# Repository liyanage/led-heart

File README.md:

Arduino LED Heart, see https://hackaday.io/project/8129-led-heart

Some code based on https://github.com/einsteinx2/arduino_heart

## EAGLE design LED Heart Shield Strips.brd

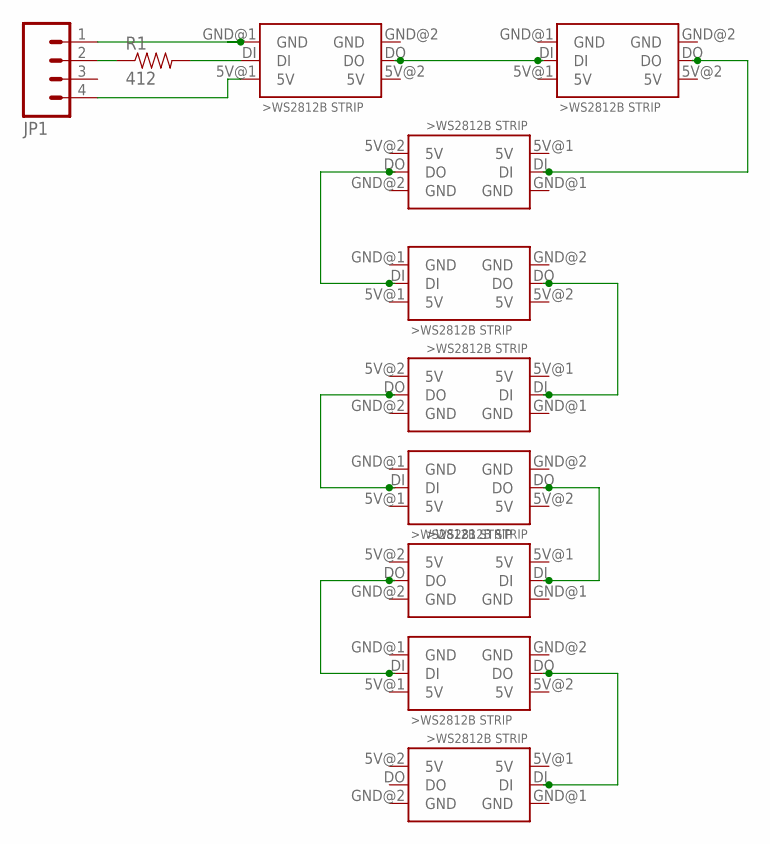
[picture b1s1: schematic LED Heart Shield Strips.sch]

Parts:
IC1, IC2, IC8: WS2812BSTRIP602; WS2812BSTRIP60_2
IC3, IC4: WS2812BSTRIP606; WS2812BSTRIP60_6
IC5: WS2812BSTRIP605; WS2812BSTRIP60_5
IC6: WS2812BSTRIP604; WS2812BSTRIP60_4
IC7: WS2812BSTRIP603; WS2812BSTRIP60_3
IC9: WS2812BSTRIP601; WS2812BSTRIP60_1
JP1: M04NO_SILK_ALL_ROUND; 1X04_NO_SILK_ALL_ROUND
R1: 412; 1206

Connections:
5V: IC1.5V@2 (5V), IC2.5V@1 (5V), IC2.5V@2 (5V), IC3.5V@1 (5V), IC3.5V@2 (5V), IC4.5V@1 (5V), IC4.5V@2 (5V), IC5.5V@1 (5V), IC5.5V@2 (5V), IC6.5V@1 (5V), IC6.5V@2 (5V), IC7.5V@1 (5V), IC7.5V@2 (5V), IC8.5V@1 (5V), IC8.5V@2 (5V), IC9.5V@1 (5V), IC9.5V@2 (5V)
GND: IC1.GND@2 (GND), IC2.GND@1 (GND), IC2.GND@2 (GND), IC3.GND@1 (GND), IC3.GND@2 (GND), IC4.GND@1 (GND), IC4.GND@2 (GND), IC5.GND@1 (GND), IC5.GND@2 (GND), IC6.GND@1 (GND), IC6.GND@2 (GND), IC7.GND@1 (GND), IC7.GND@2 (GND), IC8.GND@1 (GND), IC8.GND@2 (GND), IC9.GND@1 (GND), IC9.GND@2 (GND)
unnamed: IC1.GND@1 (GND), JP1.1
unnamed: IC1.DO, IC2.DI
unnamed: IC2.DO, IC3.DI
unnamed: IC1.5V@1 (5V), JP1.4
unnamed: IC1.DI, R1.2
unnamed: IC3.DO, IC4.DI
unnamed: IC4.DO, IC5.DI
unnamed: IC5.DO, IC6.DI
unnamed: IC6.DO, IC7.DI
unnamed: IC7.DO, IC8.DI
unnamed: IC8.DO, IC9.DI
unnamed: JP1.2, R1.1

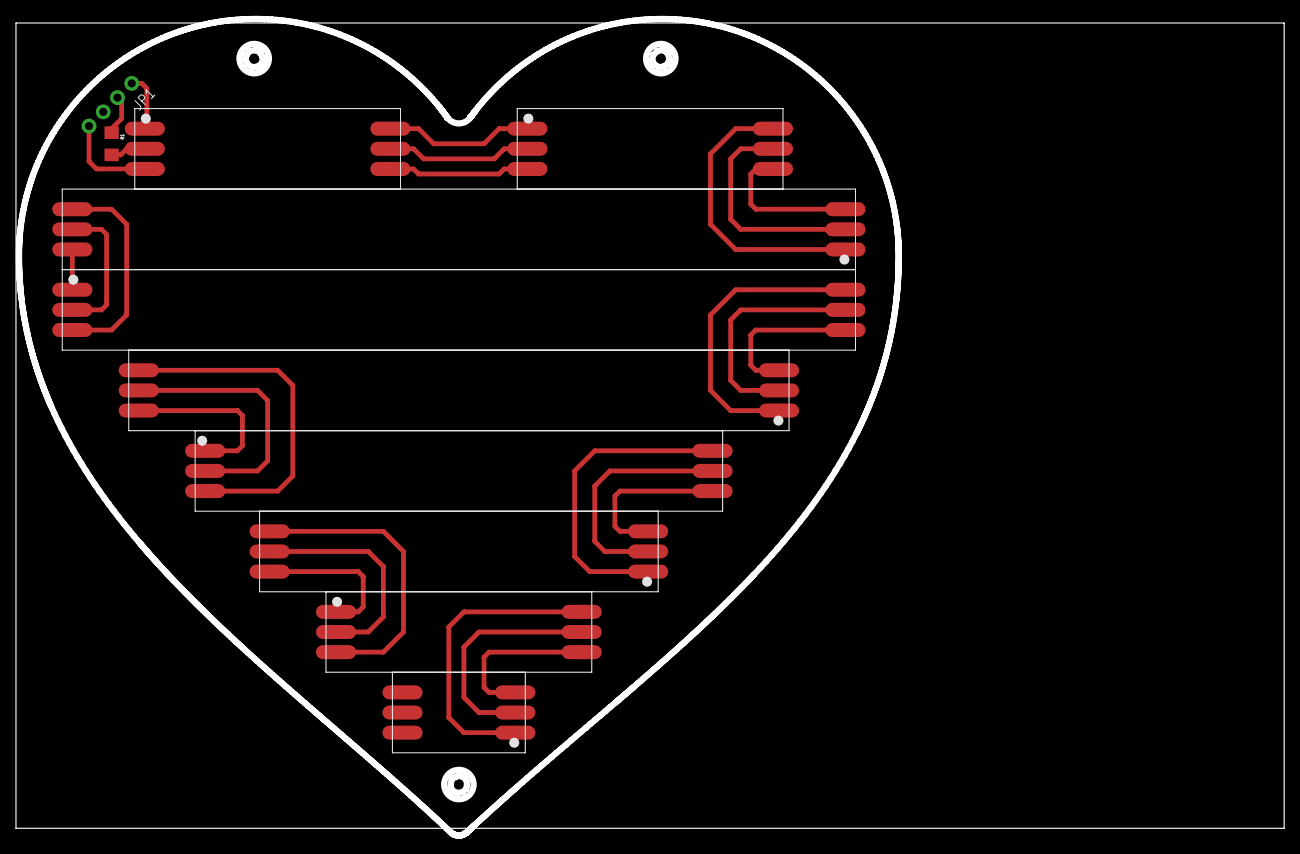
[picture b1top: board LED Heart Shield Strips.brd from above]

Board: 2 copper layers, 160.0 x 103.0 mm, 11 parts (0 on the bottom side), 14 nets.

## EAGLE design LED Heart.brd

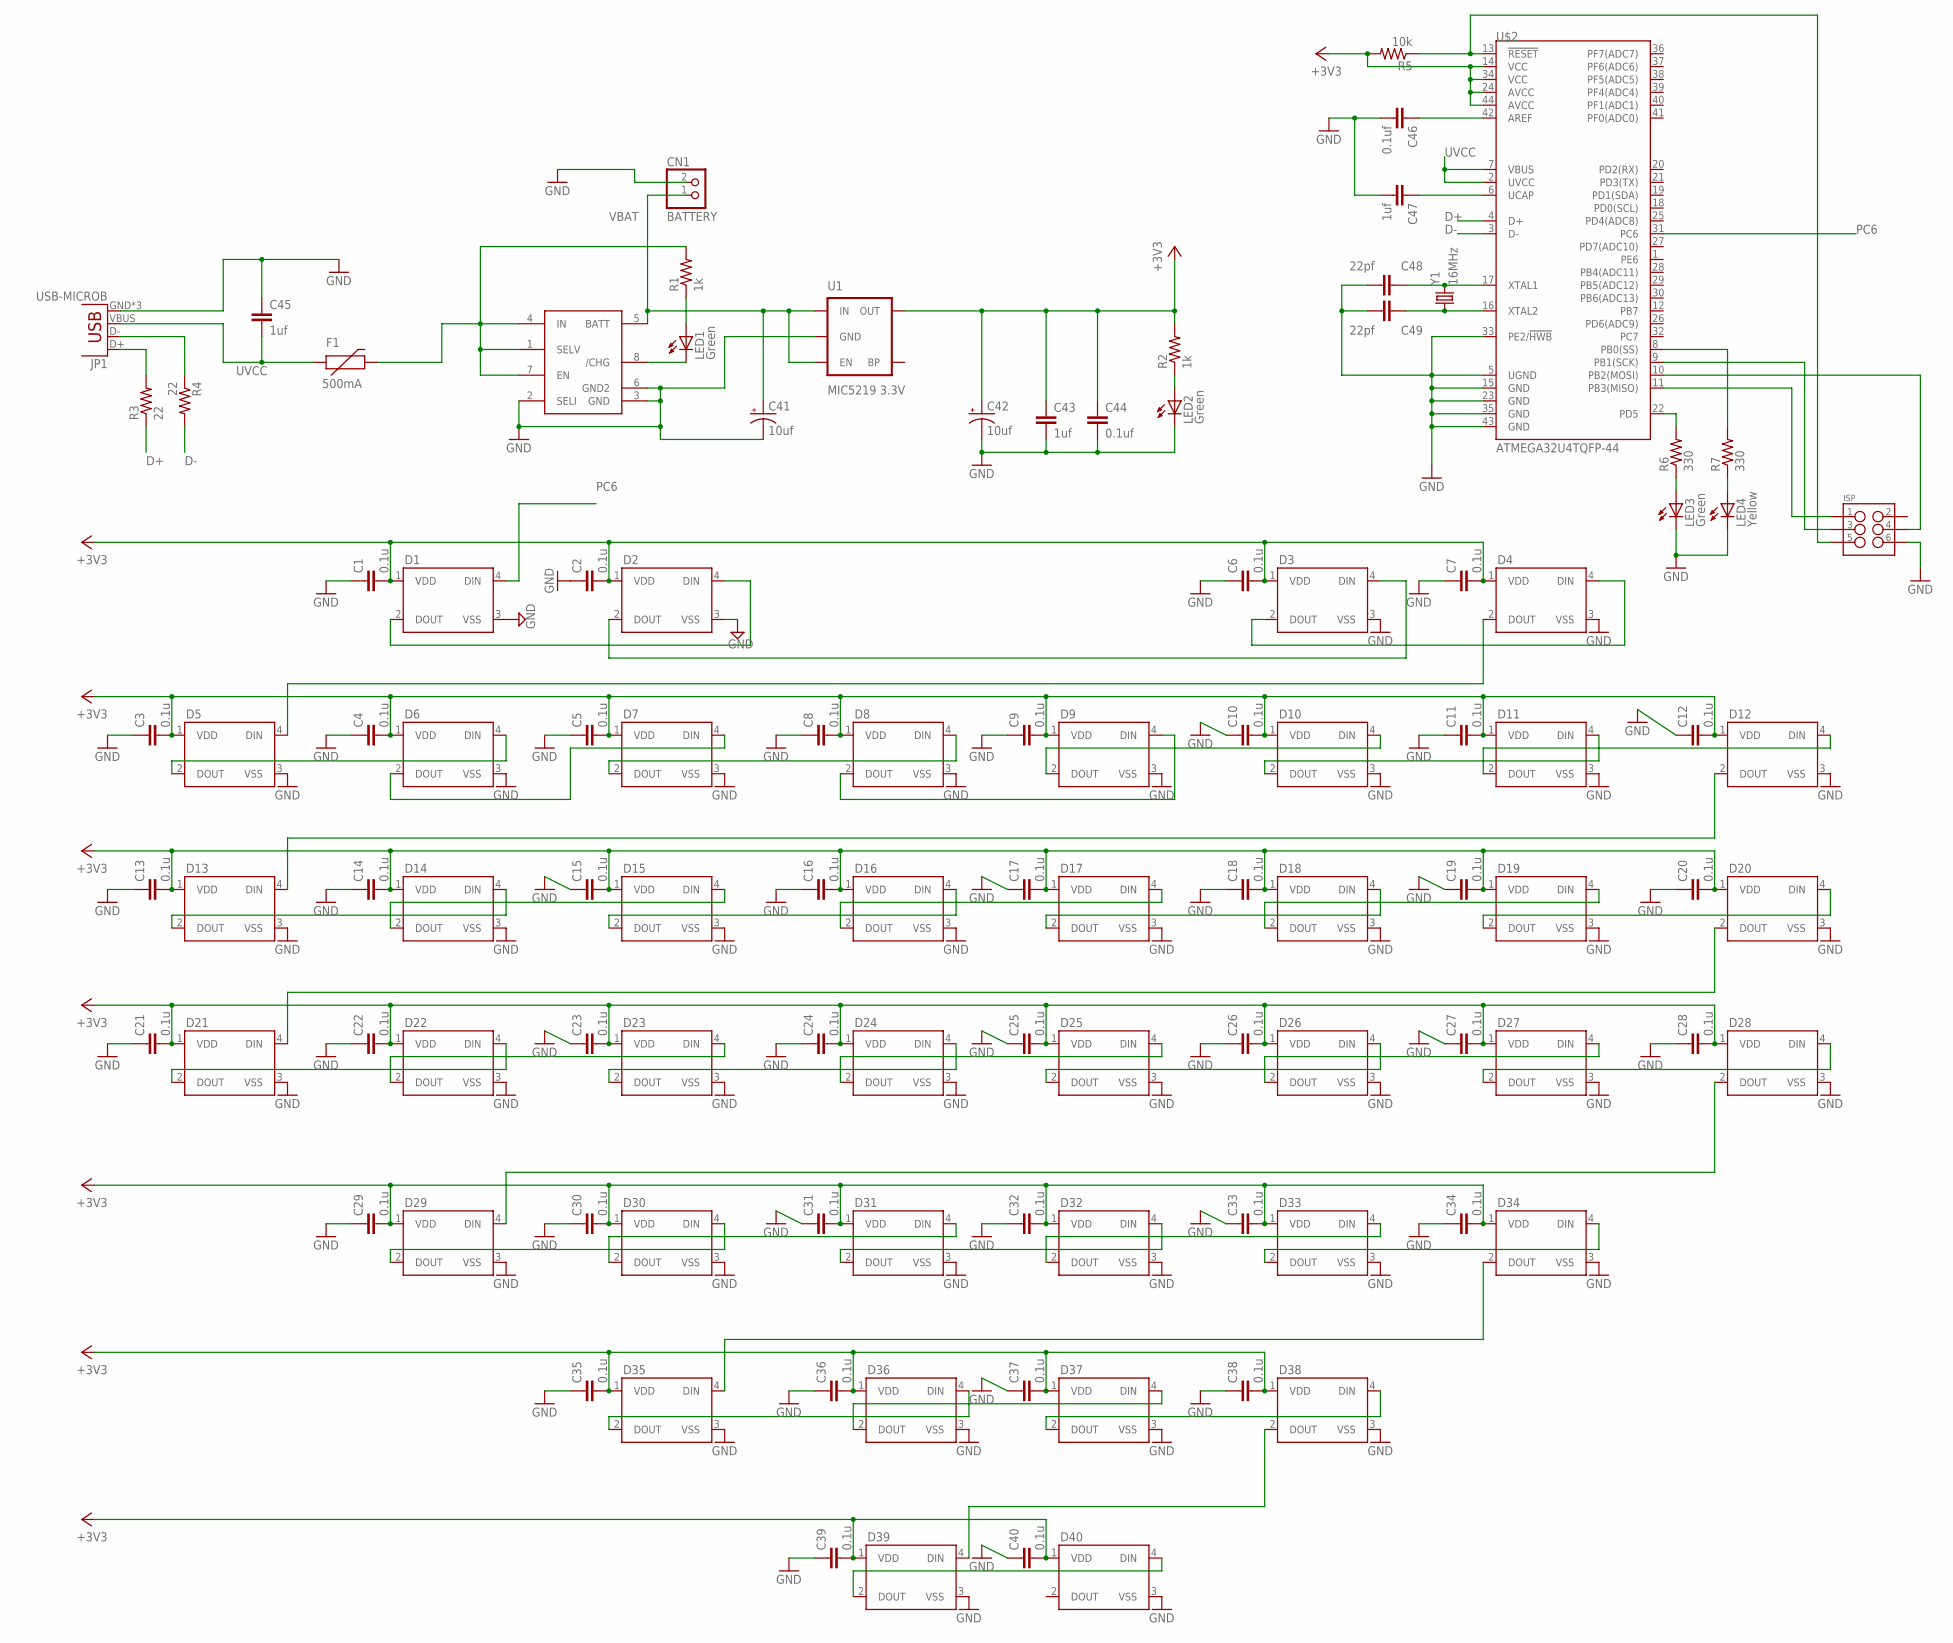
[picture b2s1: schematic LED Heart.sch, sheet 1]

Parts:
C1, C2, C3, C4, C5, C6, C7, C8, C9, C10, C11, C12, C13, C14, C15, C16, C17, C18, C19, C20, C21, C22, C23, C24, C25, C26, C27, C28, C29, C30, C31, C32, C33, C34, C35, C36, C37, C38, C39, C40: 0.1u; 0805
C41, C42: 10uf; EIA3216
C43, C45, C47: 1uf; 0805
C44, C46: 0.1uf; 0805
C48, C49: 22pf; 0805
CN1: BATTERY; JST-PH-2-SMT
D1, D2, D3, D4, D5, D6, D7, D8, D9, D10, D11, D12, D13, D14, D15, D16, D17, D18, D19, D20, D21, D22, D23, D24, D25, D26, D27, D28, D29, D30, D31, D32, D33, D34, D35, D36, D37, D38, D39, D40: WS2812B
F1: 500mA; PTC-1206
ISP: M03X2POGO_PINS; 2X3_POGO
JP1: USB-MICROB
LED1, LED2, LED3: Green; CHIP-LED0805
LED4: Yellow; CHIP-LED0805
R1, R2: 1k; 0805
R3, R4: 22; 0805
R5: 10k; 0805
R6, R7: 330; 0805
U1: MIC5219 3.3V; SOT23-5
U$1: MAX1811SO8; SO08
U$2: ATMEGA32U4TQFP-44; TQFP44
Y1: 16MHz; CRYSTAL7X5

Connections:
+3V3: C1.2, C2.2, C3.2, C4.2, C5.2, C6.2, C7.2, C8.2, C9.2, C10.2, C11.2, C12.2, C13.2, C14.2, C15.2, C16.2, C17.2, C18.2, C19.2, C20.2, C21.2, C22.2, C23.2, C24.2, C25.2, C26.2, C27.2, C28.2, C29.2, C30.2, C31.2, C32.2, C33.2, C34.2, C35.2, C36.2, C37.2, C38.2, C39.2, C40.2, C42.A (+), C43.1, C44.1, D1.1 (VDD), D2.1 (VDD), D3.1 (VDD), D4.1 (VDD), D5.1 (VDD), D6.1 (VDD), D7.1 (VDD), D8.1 (VDD), D9.1 (VDD), D10.1 (VDD), D11.1 (VDD), D12.1 (VDD), D13.1 (VDD), D14.1 (VDD), D15.1 (VDD), D16.1 (VDD), D17.1 (VDD), D18.1 (VDD), D19.1 (VDD), D20.1 (VDD), D21.1 (VDD), D22.1 (VDD), D23.1 (VDD), D24.1 (VDD), D25.1 (VDD), D26.1 (VDD), D27.1 (VDD), D28.1 (VDD), D29.1 (VDD), D30.1 (VDD), D31.1 (VDD), D32.1 (VDD), D33.1 (VDD), D34.1 (VDD), D35.1 (VDD), D36.1 (VDD), D37.1 (VDD), D38.1 (VDD), D39.1 (VDD), D40.1 (VDD), R2.2, R5.2, U1.5 (OUT), U$2.14 (VCC), U$2.24 (AVCC), U$2.34 (VCC), U$2.44 (AVCC)
D+: R3.1, U$2.4 (D+)
D-: R4.2, U$2.3 (D-)
GND: C1.1, C2.1, C3.1, C4.1, C5.1, C6.1, C7.1, C8.1, C9.1, C10.1, C11.1, C12.1, C13.1, C14.1, C15.1, C16.1, C17.1, C18.1, C19.1, C20.1, C21.1, C22.1, C23.1, C24.1, C25.1, C26.1, C27.1, C28.1, C29.1, C30.1, C31.1, C32.1, C33.1, C34.1, C35.1, C36.1, C37.1, C38.1, C39.1, C40.1, C41.C (-), C42.C (-), C43.2, C44.2, C45.1, C46.2, C47.2, C48.2, C49.2, CN1.2 (1), D1.3 (VSS), D2.3 (VSS), D3.3 (VSS), D4.3 (VSS), D5.3 (VSS), D6.3 (VSS), D7.3 (VSS), D8.3 (VSS), D9.3 (VSS), D10.3 (VSS), D11.3 (VSS), D12.3 (VSS), D13.3 (VSS), D14.3 (VSS), D15.3 (VSS), D16.3 (VSS), D17.3 (VSS), D18.3 (VSS), D19.3 (VSS), D20.3 (VSS), D21.3 (VSS), D22.3 (VSS), D23.3 (VSS), D24.3 (VSS), D25.3 (VSS), D26.3 (VSS), D27.3 (VSS), D28.3 (VSS), D29.3 (VSS), D30.3 (VSS), D31.3 (VSS), D32.3 (VSS), D33.3 (VSS), D34.3 (VSS), D35.3 (VSS), D36.3 (VSS), D37.3 (VSS), D38.3 (VSS), D39.3 (VSS), D40.3 (VSS), ISP.P$6 (6), JP1.GND, JP1.MT1 (GND), JP1.MT2 (GND), LED2.C, LED3.C, LED4.C, U1.2 (GND), U$1.2 (SELI), U$1.3 (GND), U$1.6 (GND2), U$2.5 (UGND), U$2.15 (GND), U$2.23 (GND), U$2.33 (PE2/!HWB), U$2.35 (GND), U$2.43 (GND)
unnamed: D1.2 (DOUT), D2.4 (DIN)
unnamed: D2.2 (DOUT), D3.4 (DIN)
unnamed: D3.2 (DOUT), D4.4 (DIN)
unnamed: D4.2 (DOUT), D5.4 (DIN)
unnamed: D5.2 (DOUT), D6.4 (DIN)
unnamed: D6.2 (DOUT), D7.4 (DIN)
unnamed: D7.2 (DOUT), D8.4 (DIN)
unnamed: D8.2 (DOUT), D9.4 (DIN)
unnamed: D9.2 (DOUT), D10.4 (DIN)
unnamed: D10.2 (DOUT), D11.4 (DIN)
unnamed: D11.2 (DOUT), D12.4 (DIN)
unnamed: D12.2 (DOUT), D13.4 (DIN)
unnamed: D13.2 (DOUT), D14.4 (DIN)
unnamed: D14.2 (DOUT), D15.4 (DIN)
unnamed: D15.2 (DOUT), D16.4 (DIN)
unnamed: D16.2 (DOUT), D17.4 (DIN)
unnamed: D17.2 (DOUT), D18.4 (DIN)
unnamed: D18.2 (DOUT), D19.4 (DIN)
unnamed: D19.2 (DOUT), D20.4 (DIN)
unnamed: D20.2 (DOUT), D21.4 (DIN)
unnamed: D21.2 (DOUT), D22.4 (DIN)
unnamed: D22.2 (DOUT), D23.4 (DIN)
unnamed: D23.2 (DOUT), D24.4 (DIN)
unnamed: D24.2 (DOUT), D25.4 (DIN)
unnamed: D25.2 (DOUT), D26.4 (DIN)
unnamed: D26.2 (DOUT), D27.4 (DIN)
unnamed: D27.2 (DOUT), D28.4 (DIN)
unnamed: D28.2 (DOUT), D29.4 (DIN)
unnamed: D29.2 (DOUT), D30.4 (DIN)
unnamed: D30.2 (DOUT), D31.4 (DIN)
unnamed: D31.2 (DOUT), D32.4 (DIN)
unnamed: D32.2 (DOUT), D33.4 (DIN)
unnamed: D33.2 (DOUT), D34.4 (DIN)
unnamed: D34.2 (DOUT), D35.4 (DIN)
unnamed: D35.2 (DOUT), D36.4 (DIN)
unnamed: D36.2 (DOUT), D37.4 (DIN)
unnamed: D37.2 (DOUT), D38.4 (DIN)
unnamed: D38.2 (DOUT), D39.4 (DIN)
unnamed: D39.2 (DOUT), D40.4 (DIN)
unnamed: F1.2, R1.2, U$1.1 (SELV), U$1.4 (IN), U$1.7 (EN)
unnamed: JP1.D+, R3.2
unnamed: JP1.D-, R4.1
unnamed: ISP.P$5 (5), R5.1, U$2.13 (!RESET)
unnamed: C46.1, U$2.42 (AREF)
unnamed: LED1.C, U$1.8 (/CHG)
unnamed: LED1.A, R1.1
unnamed: LED2.A, R2.1
unnamed: C47.1, U$2.6 (UCAP)
unnamed: C48.1, U$2.17 (XTAL1), Y1.3 (2)
unnamed: C49.1, U$2.16 (XTAL2), Y1.1
unnamed: ISP.P$1 (1), U$2.11 (PB3(MISO))
unnamed: ISP.P$3 (3), U$2.9 (PB1(SCK))
unnamed: ISP.P$4 (4), U$2.10 (PB2(MOSI))
unnamed: LED3.A, R6.1
unnamed: R6.2, U$2.22 (PD5)
unnamed: LED4.A, R7.1
unnamed: R7.2, U$2.8 (PB0(SS))
PC6: D1.4 (DIN), U$2.31 (PC6)
UVCC: C45.2, F1.1, JP1.VBUS, U$2.2 (UVCC), U$2.7 (VBUS)
VBAT: C41.A (+), CN1.1 (2), U1.1 (IN), U1.3 (EN), U$1.5 (BATT)

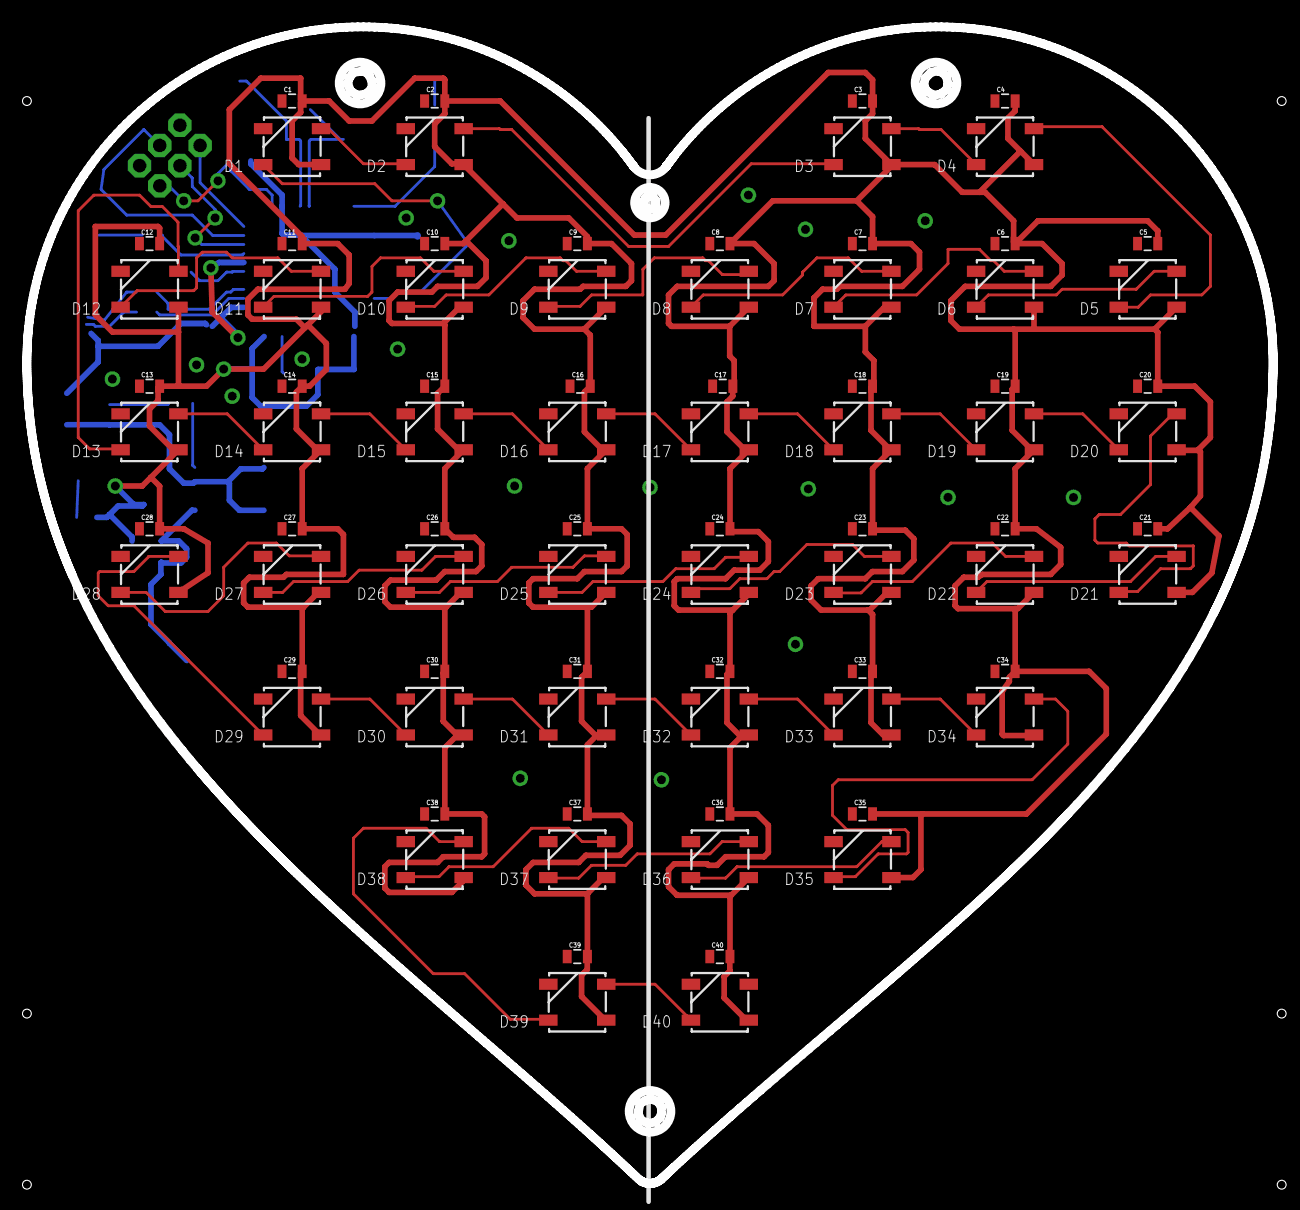
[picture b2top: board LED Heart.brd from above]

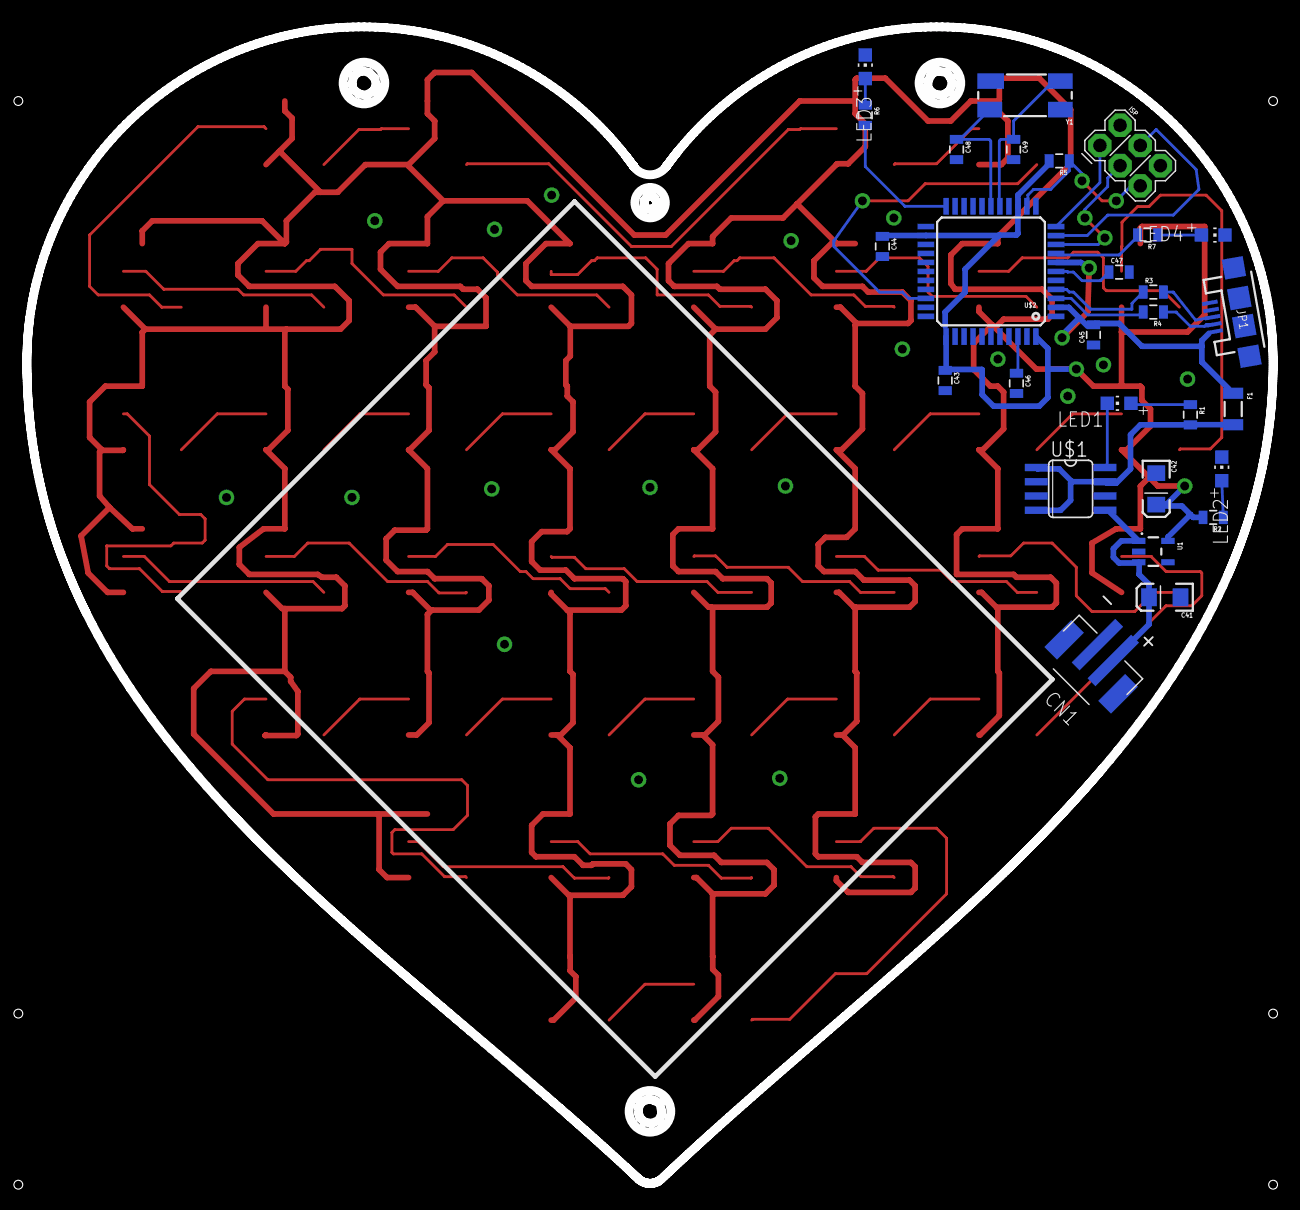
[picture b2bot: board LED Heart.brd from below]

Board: 2 copper layers, 111.0 x 103.0 mm, 108 parts (28 on the bottom side), 64 nets.

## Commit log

2015-08-27 Init
2015-08-28 More animations
2015-10-20 Add eagle files

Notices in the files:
parts and their libraries:
SparkFun-Connectors: Licensing: Creative Commons ShareAlike 4.0 International - https://creativecommons.org/licenses/by-sa/4.0
